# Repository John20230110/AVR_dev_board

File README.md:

# AVR_dev_board

The schematics of this AVR development board are mainly taken from Mao Chao's book "AVR单片机嵌入式系统原理与应用实践"("The principles and applications of AVR embedded systems") with some modifications.

The first modification is to combine the AT89S5X and Mega16 sockets to just one socket because the limitation of the space on the PCB. A 10cmX10cm PCB can be made in 10 Chinese yuan(about 1.3 US dollar) for 5 pieces by the online shop on Taobao, but the cost would soar if the size of PCB beyond that. Therefore, I put the schematics on two 10cmX10cm PCBs connected through wires. Although this division,  the space of a single board is still limited. The second modification is to add some schematics, for example a 3.3V power source and a rotator encoder.

The schematics and the PCB files of the two 10cmX10cm PCBs  are put into two directories, AVR_dev_board_main and AVR_dev_board_per_devices.  The PCB disign software used is kicad( version: 6.0.2).

In the  AVR_dev_board_main directory, there are the files of schematics and the PCB containing the MUC socket and the components connected colsely to it, for example, the crystal oscillator, the seiral connector, the power source, and the programming connector.

In the AVR_dev_board_per_devices directory, there are files of schematics and the PCB containing the peripheral devices, mainly used for input and output, such as the keyboard, the buzzer, the display, and the rotator encoder.

Here are the pictures of the first version boards. The boards are compatible to AT89s5X MCUs.

After some experiments, I found the layout, especialy PCB of the peripheral device, could be impoved.

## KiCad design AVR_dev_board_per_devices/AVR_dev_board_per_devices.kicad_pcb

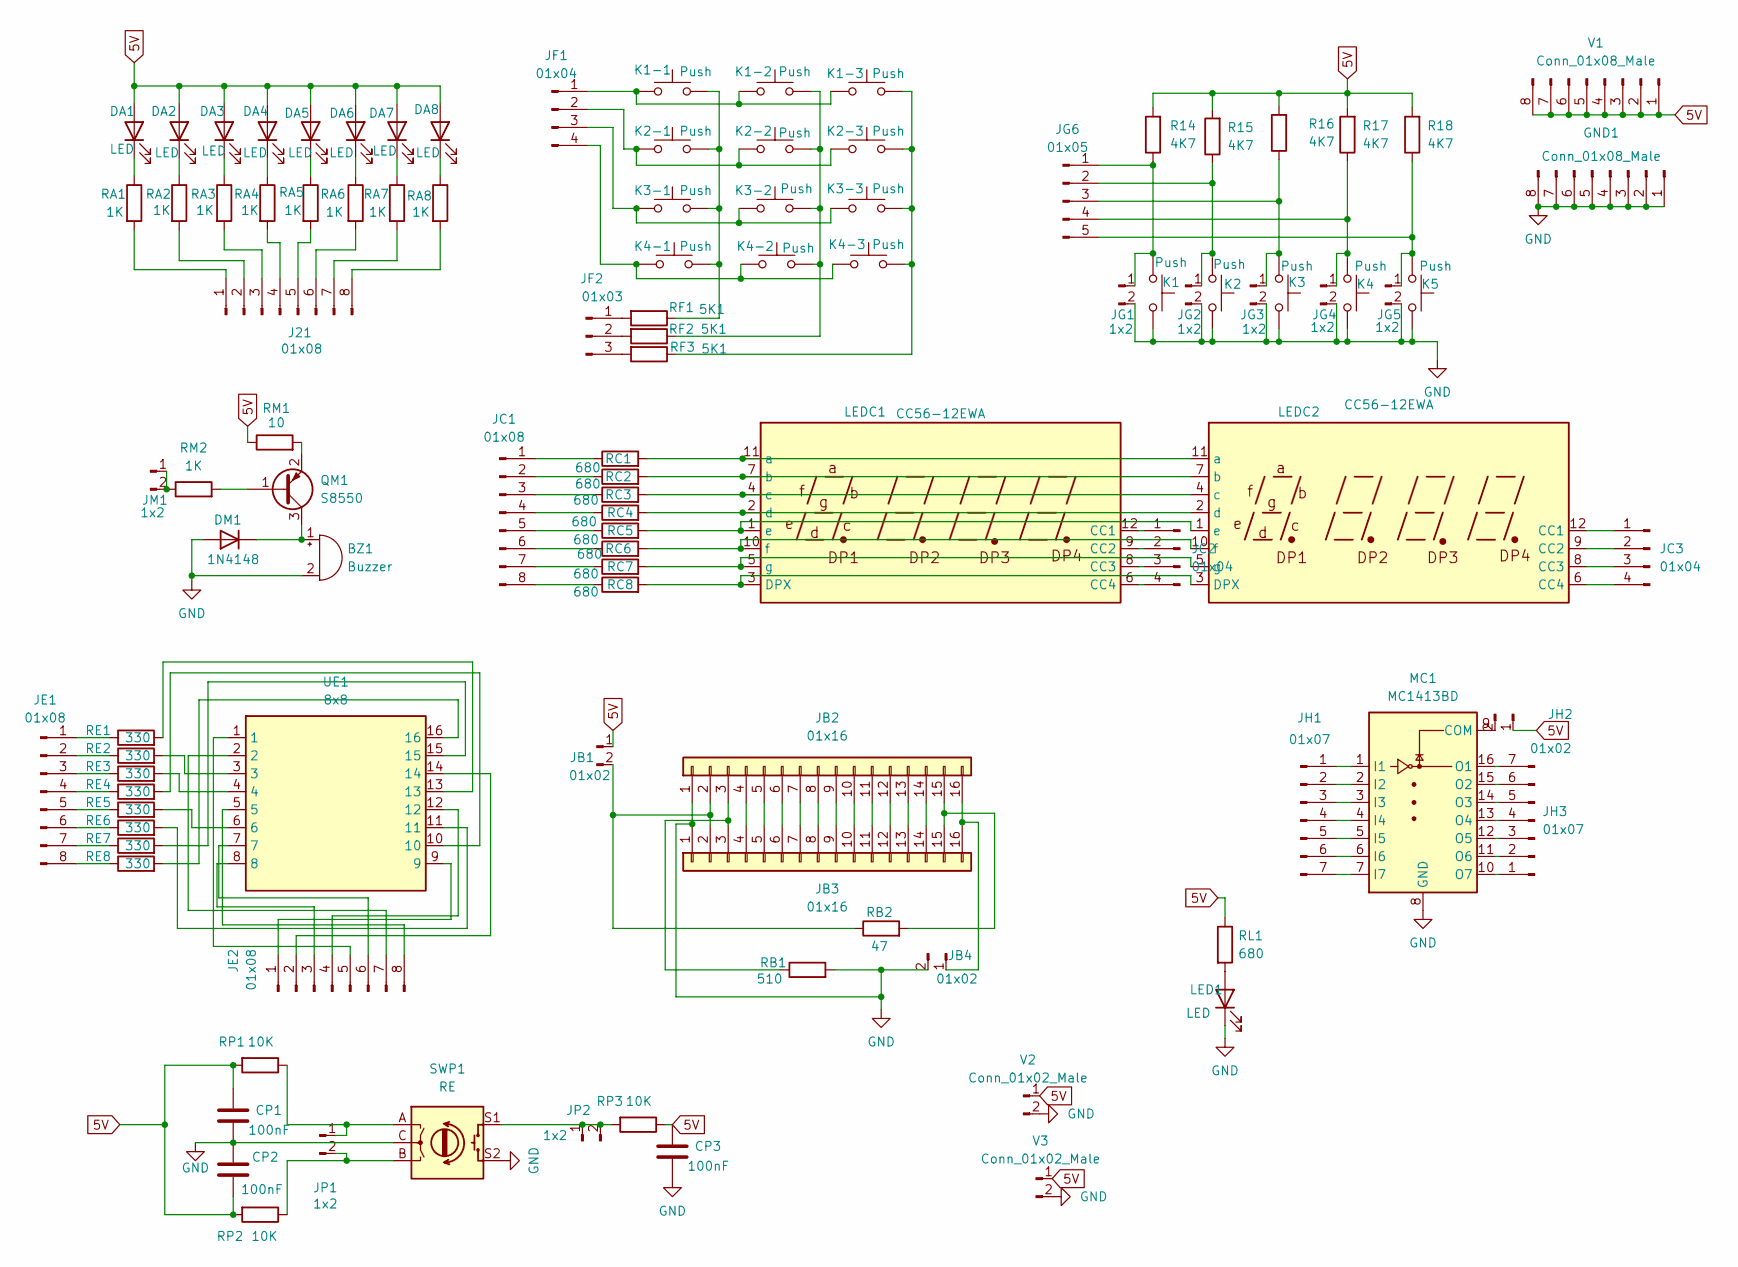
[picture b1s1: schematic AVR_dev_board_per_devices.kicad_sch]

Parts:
BZ1: Buzzer; Buzzer_TDK_PS1240P02BT_D12.2mm_H6.5mm
CP1, CP2, CP3: 100nF; C_0805_2012Metric
DA1, DA2, DA3, DA4, DA5, DA6, DA7, DA8: LED; LED_Rectangular_W3.9mm_H1.8mm
DM1: 1N4148; D_SOD-123
GND1: Conn_01x08_Male; PinHeader_1x08_P2.54mm_Vertical
J21: 01x08; PinHeader_1x08_P2.54mm_Vertical
JB1, JB4: 01x02; PinHeader_1x02_P2.54mm_Vertical
JB2: 01x16; PinHeader_1x16_P2.54mm_Vertical
JB3: 01x16; PinSocket_1x16_P2.54mm_Vertical
JC1: 01x08; PinHeader_1x08_P2.54mm_Vertical
JC2, JC3: 01x04; PinHeader_1x04_P2.54mm_Vertical
JE1, JE2: 01x08; PinHeader_1x08_P2.54mm_Vertical
JF1: 01x04; PinHeader_1x04_P2.54mm_Vertical
JF2: 01x03; PinHeader_1x03_P2.54mm_Vertical
JG1, JG2, JG3, JG4, JG5: 1x2; PinHeader_1x02_P2.54mm_Vertical
JG6: 01x05; PinHeader_1x05_P2.54mm_Vertical
JH1, JH3: 01x07; PinHeader_1x07_P2.54mm_Vertical
JH2: 01x02; PinHeader_1x02_P2.54mm_Vertical
JM1: 1x2; PinHeader_1x02_P2.54mm_Vertical
JP1, JP2: 1x2; PinHeader_1x02_P2.54mm_Vertical
K1, K1-1, K1-2, K1-3, K2, K2-1, K2-2, K2-3, K3, K3-1, K3-2, K3-3, K4, K4-1, K4-2, K4-3, K5: Push; SW_PUSH_6mm
LED1: LED; LED_D3.0mm
LEDC1, LEDC2: CC56-12EWA; 7Segment_LED_0.28inch
MC1: MC1413BD; SOP-16_3.9x9.9mm_P1.27mm
QM1: S8550; SOT-23
R14, R15, R16, R17, R18: 4K7; R_0805_2012Metric
RA1, RA2, RA3, RA4, RA5, RA6, RA7, RA8: 1K; R_0805_2012Metric
RB1: 510; R_0805_2012Metric
RB2: 47; R_0805_2012Metric
RC1, RC2, RC3, RC4, RC5, RC6, RC7, RC8: 680; R_0805_2012Metric
RE1, RE2, RE3, RE4, RE5, RE6, RE7, RE8: 330; L_0805_2012Metric
RF1, RF2, RF3: 5K1; R_0805_2012Metric
RL1: 680; R_0805_2012Metric
RM1: 10; R_0805_2012Metric
RM2: 1K; R_0805_2012Metric
RP1, RP2, RP3: 10K; R_0805_2012Metric
SWP1: RE; RotaryEncoder_Alps_EC11E-Switch_Vertical_H20mm
UE1: 8x8; dot_matrix_8x8
V1: Conn_01x08_Male; PinHeader_1x08_P2.54mm_Vertical
V2, V3: Conn_01x02_Male; PinHeader_1x02_P2.54mm_Vertical

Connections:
5V: CP1.1, CP2.2, CP3.1, DA1.2 (A), DA2.2 (A), DA3.2 (A), DA4.2 (A), DA5.2 (A), DA6.2 (A), DA7.2 (A), DA8.2 (A), JB1.1, JH2.1, R14.2, R15.2, R16.2, R17.2, R18.2, RL1.1, RM1.1, RP1.2, RP2.2, RP3.1, V1.1, V1.2, V1.3, V1.4, V1.5, V1.6, V1.7, V1.8, V2.1, V3.1
GND: BZ1.2 (+), CP1.2, CP2.1, CP3.2, DM1.2 (A), GND1.1, GND1.2, GND1.3, GND1.4, GND1.5, GND1.6, GND1.7, GND1.8, JB2.1, JB3.1, JB4.2, JG1.2, JG2.2, JG3.2, JG4.2, JG5.2, K1.2, K2.2, K3.2, K4.2, K5.2, LED1.1 (K), MC1.8 (GND), RB1.2, SWP1.C, SWP1.S2, V2.2, V3.2
unnamed: BZ1.1 (-), DM1.1 (K), QM1.3 (C)
unnamed: DA1.1 (K), RA1.1
unnamed: DA2.1 (K), RA2.1
unnamed: DA3.1 (K), RA3.1
unnamed: DA4.1 (K), RA4.1
unnamed: DA5.1 (K), RA5.1
unnamed: DA6.1 (K), RA6.1
unnamed: DA7.1 (K), RA7.1
unnamed: DA8.1 (K), RA8.1
unnamed: J21.1, RA1.2
unnamed: J21.2, RA2.2
unnamed: J21.3, RA3.2
unnamed: J21.4, RA4.2
unnamed: J21.5, RA5.2
unnamed: J21.6, RA6.2
unnamed: J21.7, RA7.2
unnamed: J21.8, RA8.2
unnamed: JB1.2, JB2.2, JB3.2, RB2.1
unnamed: JB2.3, JB3.3, RB1.1
unnamed: JB2.4, JB3.4
unnamed: JB2.5, JB3.5
unnamed: JB2.6, JB3.6
unnamed: JB2.7, JB3.7
unnamed: JB2.8, JB3.8
unnamed: JB2.9, JB3.9
unnamed: JB2.10, JB3.10
unnamed: JB2.11, JB3.11
unnamed: JB2.12, JB3.12
unnamed: JB2.13, JB3.13
unnamed: JB2.14, JB3.14
unnamed: JB2.15, JB3.15, RB2.2
unnamed: JB2.16, JB3.16, JB4.1
unnamed: JC1.1, RC1.1
unnamed: JC1.2, RC2.1
unnamed: JC1.3, RC3.1
unnamed: JC1.4, RC4.1
unnamed: JC1.5, RC5.1
unnamed: JC1.6, RC6.1
unnamed: JC1.7, RC7.1
unnamed: JC1.8, RC8.1
unnamed: JC2.1, LEDC1.12 (CC1)
unnamed: JC2.2, LEDC1.9 (CC2)
unnamed: JC2.3, LEDC1.8 (CC3)
unnamed: JC2.4, LEDC1.6 (CC4)
unnamed: JC3.1, LEDC2.12 (CC1)
unnamed: JC3.2, LEDC2.9 (CC2)
unnamed: JC3.3, LEDC2.8 (CC3)
unnamed: JC3.4, LEDC2.6 (CC4)
unnamed: JE1.1, RE1.1
unnamed: JE1.2, RE2.1
unnamed: JE1.3, RE3.1
unnamed: JE1.4, RE4.1
unnamed: JE1.5, RE5.1
unnamed: JE1.6, RE6.1
unnamed: JE1.7, RE7.1
unnamed: JE1.8, RE8.1
unnamed: JE2.1, UE1.9
unnamed: JE2.2, UE1.14
unnamed: JE2.3, UE1.8
unnamed: JE2.4, UE1.12
unnamed: JE2.5, UE1.1
unnamed: JE2.6, UE1.7
unnamed: JE2.7, UE1.2
unnamed: JE2.8, UE1.5
unnamed: JF1.1, K1-1.1, K1-2.1, K1-3.1
unnamed: JF1.2, K2-1.1, K2-2.1, K2-3.1
unnamed: JF1.3, K3-1.1, K3-2.1, K3-3.1
unnamed: JF1.4, K4-1.1, K4-2.1, K4-3.1
unnamed: JF2.1, RF1.2
unnamed: JF2.2, RF2.2
unnamed: JF2.3, RF3.2
unnamed: JG1.1, JG6.1, K1.1, R14.1
unnamed: JG2.1, JG6.2, K2.1, R15.1
unnamed: JG4.1, JG6.4, K4.1, R17.1
unnamed: JG5.1, JG6.5, K5.1, R18.1
unnamed: JG3.1, JG6.3, K3.1, R16.1
unnamed: JH1.1, MC1.1 (I1)
unnamed: JH1.2, MC1.2 (I2)
unnamed: JH1.3, MC1.3 (I3)
unnamed: JH1.4, MC1.4 (I4)
unnamed: JH1.5, MC1.5 (I5)
unnamed: JH1.6, MC1.6 (I6)
unnamed: JH1.7, MC1.7 (I7)
unnamed: JH2.2, MC1.9 (COM)
unnamed: JH3.1, MC1.10 (O7)
unnamed: JH3.2, MC1.11 (O6)
unnamed: JH3.3, MC1.12 (O5)
unnamed: JH3.4, MC1.13 (O4)
unnamed: JH3.5, MC1.14 (O3)
unnamed: JH3.6, MC1.15 (O2)
unnamed: JH3.7, MC1.16 (O1)
unnamed: JM1.1, JM1.2, RM2.1
unnamed: JP1.1, RP1.1, SWP1.A
unnamed: JP1.2, RP2.1, SWP1.B
unnamed: JP2.1, JP2.2, RP3.2, SWP1.S1
unnamed: K1-1.2, K2-1.2, K3-1.2, K4-1.2, RF1.1
unnamed: K1-2.2, K2-2.2, K3-2.2, K4-2.2, RF2.1
unnamed: K1-3.2, K2-3.2, K3-3.2, K4-3.2, RF3.1
unnamed: LED1.2 (A), RL1.2
unnamed: LEDC1.1 (e), LEDC2.1 (e), RC5.2
unnamed: LEDC1.2 (d), LEDC2.2 (d), RC4.2
unnamed: LEDC1.3 (DPX), LEDC2.3 (DPX), RC8.2
unnamed: LEDC1.4 (c), LEDC2.4 (c), RC3.2
unnamed: LEDC1.5 (g), LEDC2.5 (g), RC7.2
unnamed: LEDC1.7 (b), LEDC2.7 (b), RC2.2
unnamed: LEDC1.10 (f), LEDC2.10 (f), RC6.2
unnamed: LEDC1.11 (a), LEDC2.11 (a), RC1.2
unnamed: QM1.1 (B), RM2.2
unnamed: QM1.2 (E), RM1.2
unnamed: RE1.2, UE1.13
unnamed: RE2.2, UE1.3
unnamed: RE3.2, UE1.4
unnamed: RE4.2, UE1.10
unnamed: RE5.2, UE1.6
unnamed: RE6.2, UE1.11
unnamed: RE7.2, UE1.15
unnamed: RE8.2, UE1.16

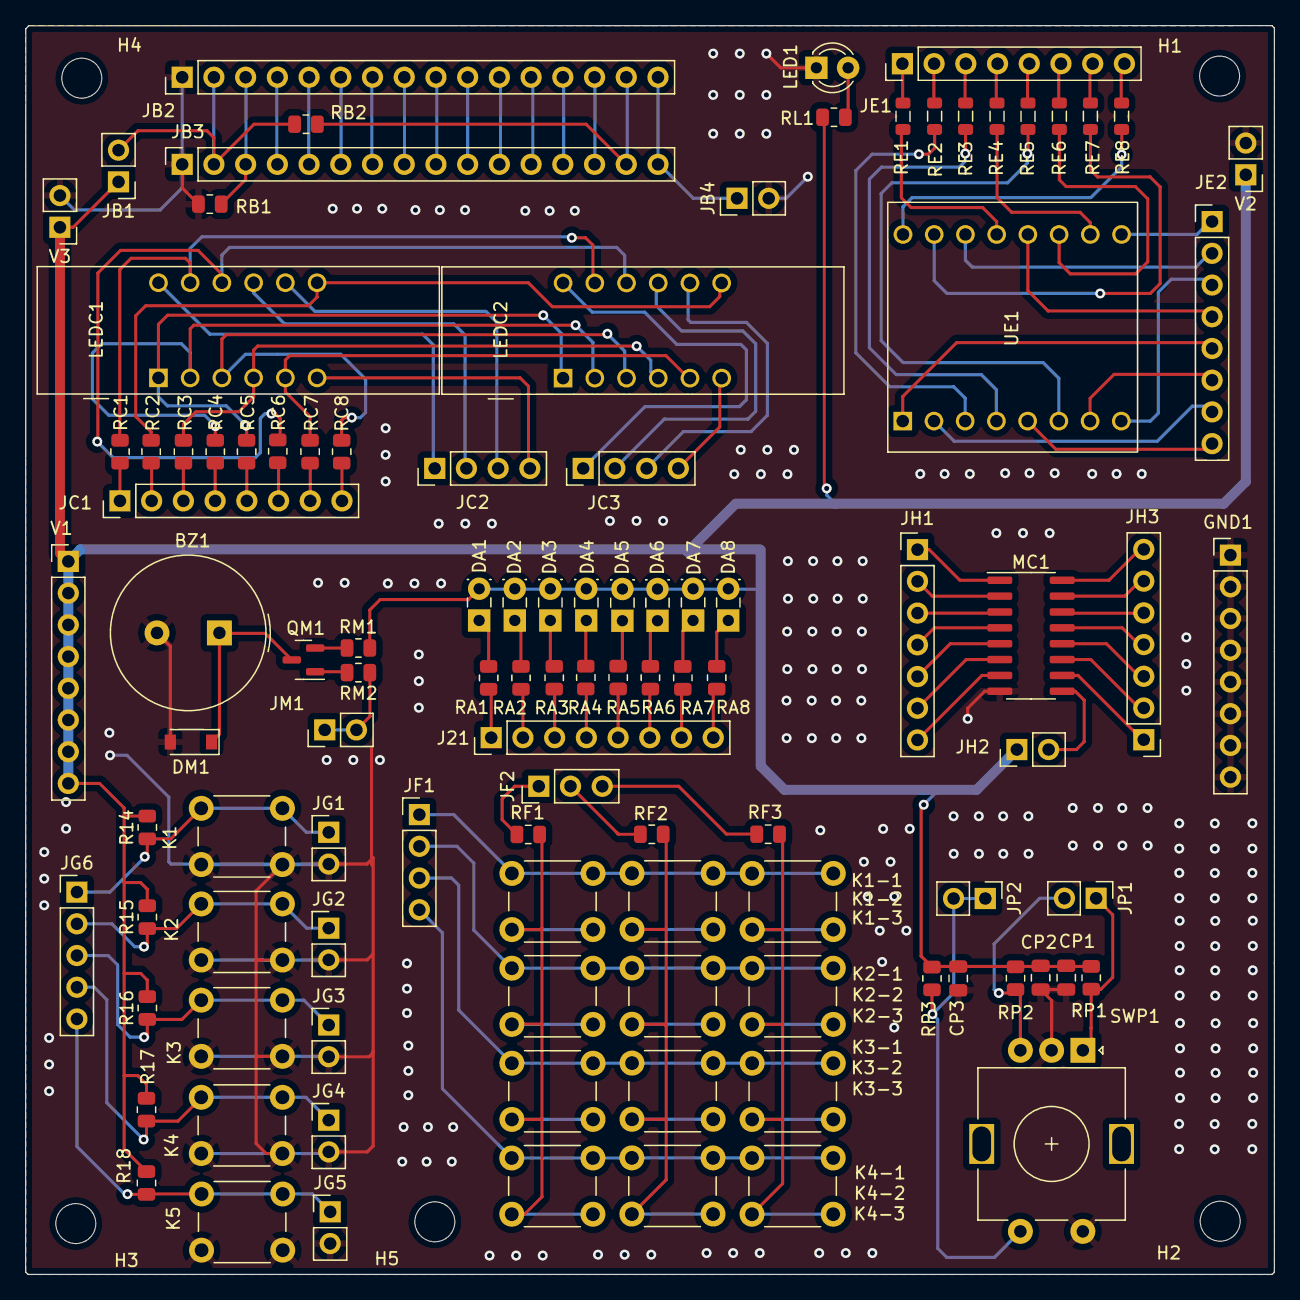
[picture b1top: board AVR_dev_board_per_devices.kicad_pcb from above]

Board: 2 copper layers, 100.0 x 100.0 mm, 110 parts (0 on the bottom side), 119 nets.

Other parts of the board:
H1, H2, H3, H4, H5: MountingHole_3.2mm_M3

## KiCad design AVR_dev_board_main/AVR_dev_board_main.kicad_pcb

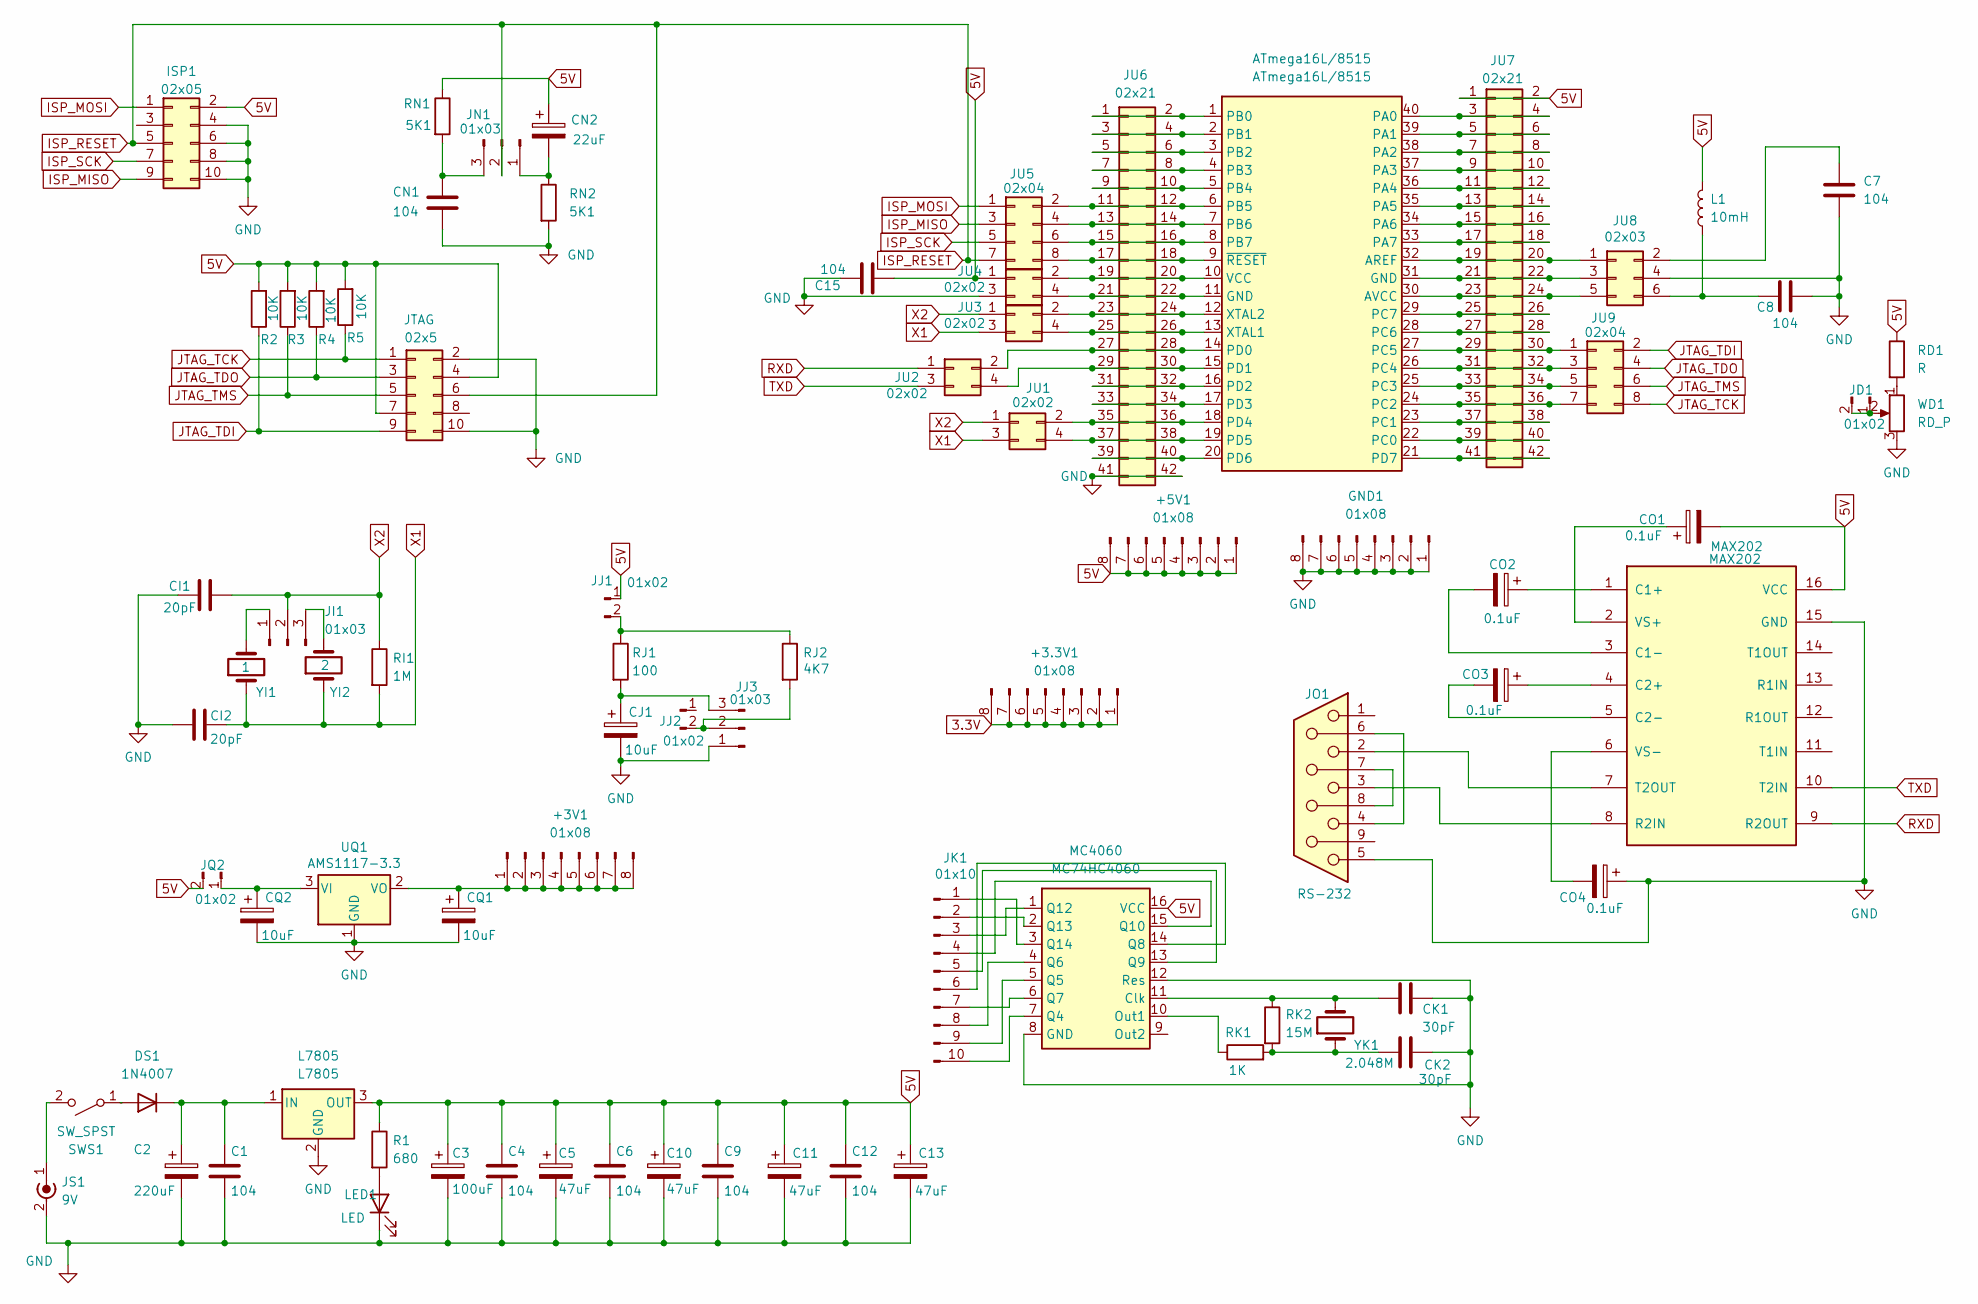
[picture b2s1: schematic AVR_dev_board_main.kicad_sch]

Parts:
02x5: JTAG; IDC-Socket_2x05_P2.54mm
+3.3V1, +3V1, +5V1: 01x08; PinHeader_1x08_P2.54mm_Vertical
ATmega16L/8515: ATmega16L/8515; 3M_Textool_240-1288-00-0602J_2x20_P2.54mm
C1, C4, C6, C7, C8, C9, C12, C15: 104; C_0805_2012Metric
C2: 220uF; CP_Elec_8x10.5
C3: 100uF; CP_Elec_6.3x5.4
C5, C10, C11, C13: 47uF; CP_Elec_5x5.4
CI1, CI2: 20pF; C_0805_2012Metric
CJ1: 10uF; CP_Elec_4x5.4
CK1, CK2: 30pF; C_0805_2012Metric
CN1: 104; C_0805_2012Metric
CN2: 22uF; CP_Elec_5x5.4
CO1, CO2, CO3, CO4: 0.1uF; CP_Elec_4x5.4
CQ1, CQ2: 10uF; CP_Elec_4x5.4
DS1: 1N4007; D_SOD-123
GND1: 01x08; PinHeader_1x08_P2.54mm_Vertical
ISP1: 02x05; IDC-Socket_2x05_P2.54mm
JD1: 01x02; PinHeader_1x02_P2.54mm_Vertical
JI1: 01x03; PinHeader_1x03_P2.54mm_Vertical
JJ1, JJ2: 01x02; PinHeader_1x02_P2.54mm_Vertical
JJ3: 01x03; PinHeader_1x03_P2.54mm_Vertical
JK1: 01x10; PinHeader_1x10_P2.54mm_Vertical
JN1: 01x03; PinHeader_1x03_P2.54mm_Vertical
JO1: RS-232; DSUB-9_Female_Horizontal_P2.77x2.84mm_EdgePinOffset7.70mm_H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
JQ2: 01x02; PinHeader_1x02_P2.54mm_Vertical
JS1: 9V; BarrelJack_Horizontal
JU1, JU2, JU3, JU4: 02x02; PinHeader_2x02_P2.54mm_Vertical
JU5, JU9: 02x04; PinHeader_2x04_P2.54mm_Vertical
JU6, JU7: 02x21; PinHeader_2x21_P2.54mm_Vertical
JU8: 02x03; PinHeader_2x03_P2.54mm_Vertical
L1: 10mH; L_Radial_D8.7mm_P5.00mm_Fastron_07HCP
L7805: L7805; TO-220-3_Vertical
LED1: LED; LED_D3.0mm
MAX202: MAX202; SOP-16_3.9x9.9mm_P1.27mm
MC4060: MC74HC4060; SOP-16_3.9x9.9mm_P1.27mm
R1: 680; R_0805_2012Metric
R2, R3, R4, R5: 10K; R_0805_2012Metric
RD1: R; R_0805_2012Metric
RI1: 1M; R_0805_2012Metric
RJ1: 100; R_0805_2012Metric
RJ2: 4K7; R_0805_2012Metric
RK1: 1K; R_0805_2012Metric
RK2: 15M; R_0805_2012Metric
RN1, RN2: 5K1; R_0805_2012Metric
SWS1: SW_SPST; SW_Slide_1P2T_CK_OS102011MS2Q
UQ1: AMS1117-3.3; SOT-223-3_TabPin2
WD1: RD_P; Potentiometer_Bourns_3296W_Vertical
YI1: 1; Crystal_HC18-U_Vertical
YI2: 2; Crystal_HC18-U_Vertical
YK1: 2.048M; Crystal_HC18-U_Horizontal_1EP_style2

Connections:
5V: 02x5.4, 02x5.7, +5V1.1, +5V1.2, +5V1.3, +5V1.4, +5V1.5, +5V1.6, +5V1.7, +5V1.8, C3.1, C4.1, C5.1, C6.1, C9.1, C10.1, C11.1, C12.1, C13.1, C15.2, CN2.1, CO1.2, ISP1.2, JJ1.1, JQ2.2, JU4.1, JU7.1, JU7.2, L1.2, L7805.3 (OUT), MAX202.16 (VCC), MC4060.16 (VCC), R1.1, R2.2, R3.2, R4.2, R5.2, RD1.1, RN1.1
GND: 02x5.2, 02x5.10, C1.2, C2.2, C3.2, C4.2, C5.2, C6.2, C7.1, C8.2, C9.2, C10.2, C11.2, C12.2, C13.2, C15.1, CI1.2, CI2.1, CJ1.2, CK1.2, CK2.2, CN1.2, CO4.1, CQ1.2, CQ2.2, GND1.1, GND1.2, GND1.3, GND1.4, GND1.5, GND1.6, GND1.7, GND1.8, ISP1.4, ISP1.6, ISP1.8, ISP1.10, JJ3.1, JO1.5, JS1.2 (Ext), JU4.3, JU6.41, JU6.42, JU8.4, L7805.2 (GND), LED1.1 (K), MAX202.15 (GND), MC4060.8 (GND), MC4060.12 (Res), RN2.2, UQ1.1 (GND), WD1.3
ISP_MISO: ISP1.9, JU5.3
ISP_MOSI: ISP1.1, JU5.1
ISP_RESET: 02x5.6, ISP1.5, JN1.2, JU5.7
ISP_SCK: ISP1.7, JU5.5
JTAG_TCK: 02x5.1, JU9.8, R5.1
JTAG_TDI: 02x5.9, JU9.2, R2.1
JTAG_TDO: 02x5.3, JU9.4, R4.1
JTAG_TMS: 02x5.5, JU9.6, R3.1
unnamed: +3.3V1.1, +3.3V1.2, +3.3V1.3, +3.3V1.4, +3.3V1.5, +3.3V1.6, +3.3V1.7, +3.3V1.8
unnamed: ATmega16L/8515.1 (PB0), JU6.1, JU6.2
unnamed: ATmega16L/8515.2 (PB1), JU6.3, JU6.4
unnamed: ATmega16L/8515.3 (PB2), JU6.5, JU6.6
unnamed: ATmega16L/8515.4 (PB3), JU6.7, JU6.8
unnamed: ATmega16L/8515.5 (PB4), JU6.9, JU6.10
unnamed: ATmega16L/8515.6 (PB5), JU5.2, JU6.11, JU6.12
unnamed: ATmega16L/8515.7 (PB6), JU5.4, JU6.13, JU6.14
unnamed: ATmega16L/8515.8 (PB7), JU5.6, JU6.15, JU6.16
unnamed: ATmega16L/8515.9 (~RESET), JU5.8, JU6.17, JU6.18
unnamed: ATmega16L/8515.10 (VCC), JU4.2, JU6.19, JU6.20
unnamed: ATmega16L/8515.11 (GND), JU4.4, JU6.21, JU6.22
unnamed: ATmega16L/8515.12 (XTAL2), JU3.2, JU6.23, JU6.24
unnamed: ATmega16L/8515.13 (XTAL1), JU3.4, JU6.25, JU6.26
unnamed: ATmega16L/8515.14 (PD0), JU2.2, JU6.27, JU6.28
unnamed: ATmega16L/8515.15 (PD1), JU2.4, JU6.29, JU6.30
unnamed: ATmega16L/8515.16 (PD2), JU6.31, JU6.32
unnamed: ATmega16L/8515.17 (PD3), JU6.33, JU6.34
unnamed: ATmega16L/8515.18 (PD4), JU1.2, JU6.35, JU6.36
unnamed: ATmega16L/8515.19 (PD5), JU1.4, JU6.37, JU6.38
unnamed: ATmega16L/8515.20 (PD6), JU6.39, JU6.40
unnamed: ATmega16L/8515.21 (PD7), JU7.41, JU7.42
unnamed: ATmega16L/8515.22 (PC0), JU7.39, JU7.40
unnamed: ATmega16L/8515.23 (PC1), JU7.37, JU7.38
unnamed: ATmega16L/8515.24 (PC2), JU7.35, JU7.36, JU9.7
unnamed: ATmega16L/8515.25 (PC3), JU7.33, JU7.34, JU9.5
unnamed: ATmega16L/8515.26 (PC4), JU7.31, JU7.32, JU9.3
unnamed: ATmega16L/8515.27 (PC5), JU7.29, JU7.30, JU9.1
unnamed: ATmega16L/8515.28 (PC6), JU7.27, JU7.28
unnamed: ATmega16L/8515.29 (PC7), JU7.25, JU7.26
unnamed: ATmega16L/8515.30 (AVCC), JU7.23, JU7.24, JU8.5
unnamed: ATmega16L/8515.31 (GND), JU7.21, JU7.22, JU8.3
unnamed: ATmega16L/8515.32 (AREF), JU7.19, JU7.20, JU8.1
unnamed: ATmega16L/8515.33 (PA7), JU7.17, JU7.18
unnamed: ATmega16L/8515.34 (PA6), JU7.15, JU7.16
unnamed: ATmega16L/8515.35 (PA5), JU7.13, JU7.14
unnamed: ATmega16L/8515.36 (PA4), JU7.11, JU7.12
unnamed: ATmega16L/8515.37 (PA3), JU7.9, JU7.10
unnamed: ATmega16L/8515.38 (PA2), JU7.7, JU7.8
unnamed: ATmega16L/8515.39 (PA1), JU7.5, JU7.6
unnamed: ATmega16L/8515.40 (PA0), JU7.3, JU7.4
unnamed: C1.1, C2.1, DS1.1 (K), L7805.1 (IN)
unnamed: C7.2, JU8.2
unnamed: C8.1, JU8.6, L1.1
unnamed: CJ1.1, JJ3.3, RJ1.2
unnamed: CK1.1, MC4060.11 (Clk), RK2.1, YK1.2
unnamed: CK2.1, RK1.2, RK2.2, YK1.1
unnamed: CN1.1, JN1.3, RN1.2
unnamed: CN2.2, JN1.1, RN2.1
unnamed: CO1.1, MAX202.2 (VS+)
unnamed: CO2.1, MAX202.1 (C1+)
unnamed: CO2.2, MAX202.3 (C1-)
unnamed: CO3.1, MAX202.4 (C2+)
unnamed: CO3.2, MAX202.5 (C2-)
unnamed: CO4.2, MAX202.6 (VS-)
unnamed: +3V1.1, +3V1.2, +3V1.3, +3V1.4, +3V1.5, +3V1.6, +3V1.7, +3V1.8, CQ1.1, UQ1.2 (VO)
unnamed: CQ2.1, JQ2.1, UQ1.3 (VI)
unnamed: DS1.2 (A), SWS1.1 (A)
unnamed: JD1.1, JD1.2, WD1.2
unnamed: JI1.1, YI1.2
unnamed: JI1.3, YI2.2
unnamed: JJ1.2, RJ1.1, RJ2.1
unnamed: JJ2.2, JJ3.2, RJ2.2
unnamed: JK1.1, MC4060.3 (Q14)
unnamed: JK1.2, MC4060.2 (Q13)
unnamed: JK1.3, MC4060.1 (Q12)
unnamed: JK1.4, MC4060.15 (Q10)
unnamed: JK1.5, MC4060.13 (Q9)
unnamed: JK1.6, MC4060.14 (Q8)
unnamed: JK1.7, MC4060.6 (Q7)
unnamed: JK1.8, MC4060.4 (Q6)
unnamed: JK1.9, MC4060.5 (Q5)
unnamed: JK1.10, MC4060.7 (Q4)
unnamed: JO1.2, MAX202.7 (T2OUT)
unnamed: JO1.3, MAX202.8 (R2IN)
unnamed: JO1.4, JO1.6
unnamed: JO1.7, JO1.8
unnamed: JS1.1 (In), SWS1.2 (B)
unnamed: LED1.2 (A), R1.2
unnamed: MC4060.10 (Out1), RK1.1
unnamed: RD1.2, WD1.1
RXD: JU2.1, MAX202.9 (R2OUT)
TXD: JU2.3, MAX202.10 (T2IN)
X1: CI2.2, JU1.3, JU3.3, RI1.2, YI1.1, YI2.1
X2: CI1.1, JI1.2, JU1.1, JU3.1, RI1.1

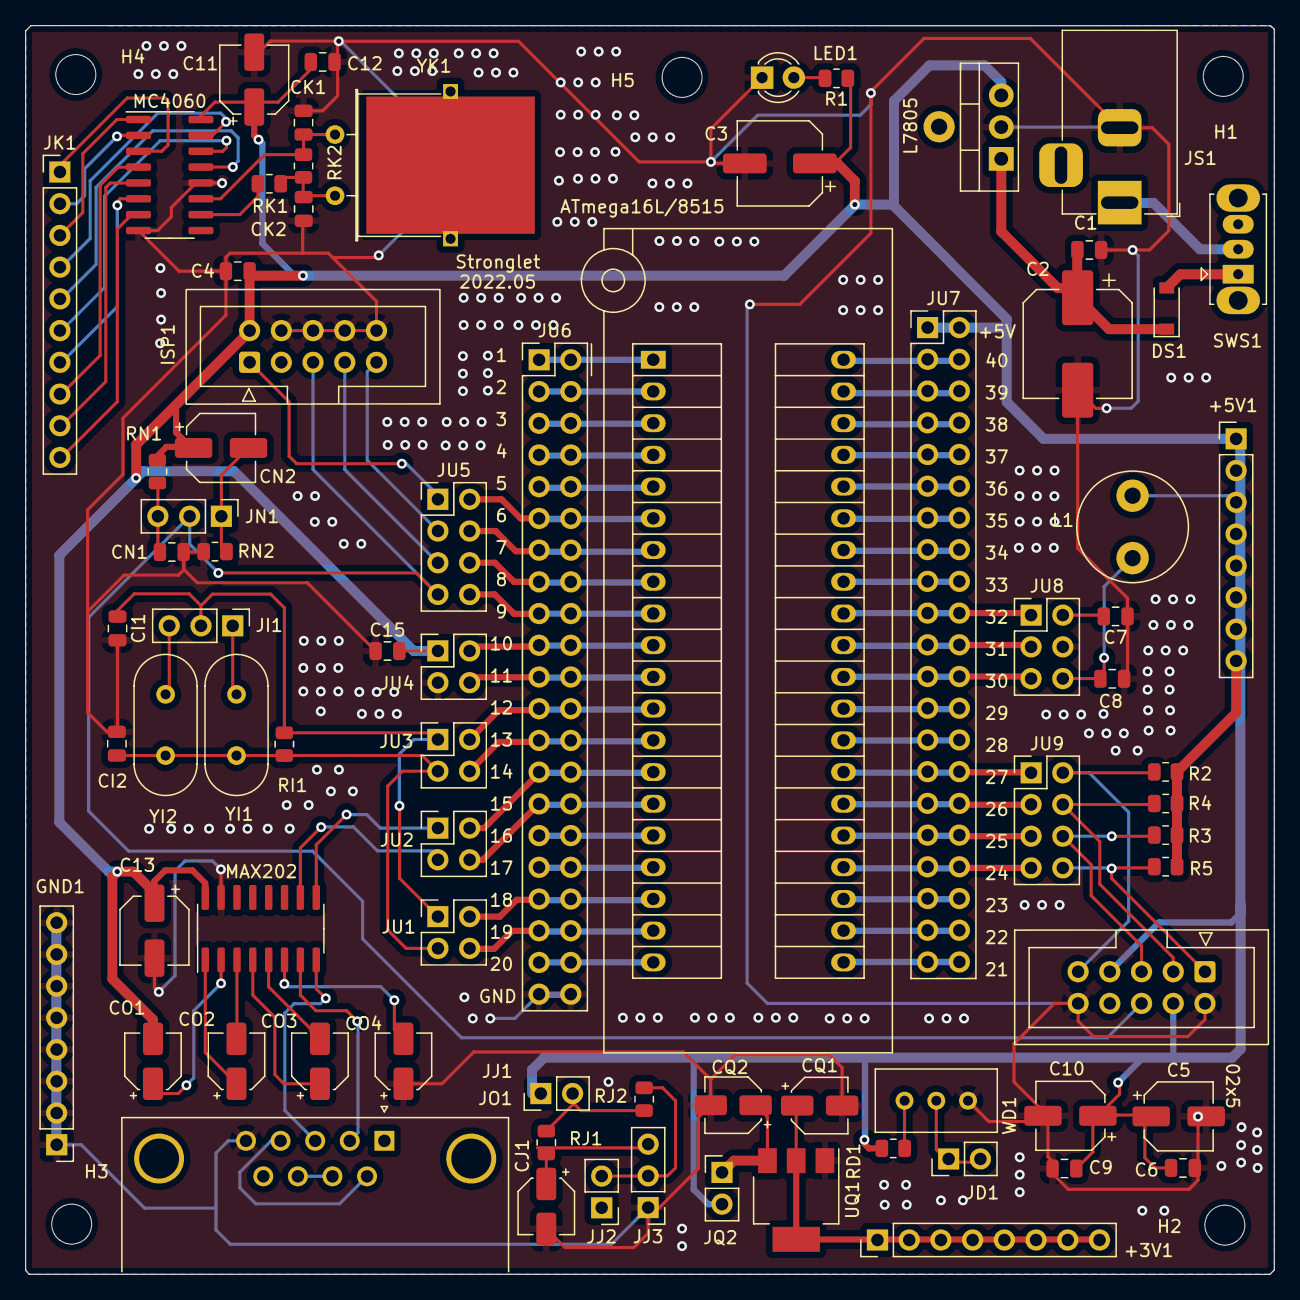
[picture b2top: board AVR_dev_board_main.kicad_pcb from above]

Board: 2 copper layers, 100.0 x 100.0 mm, 82 parts (0 on the bottom side), 94 nets.

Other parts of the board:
H1, H2, H3, H4, H5: MountingHole_3.2mm_M3

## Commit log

2023-07-29 init
2023-07-29 odify readme
2023-07-29 modify readme
